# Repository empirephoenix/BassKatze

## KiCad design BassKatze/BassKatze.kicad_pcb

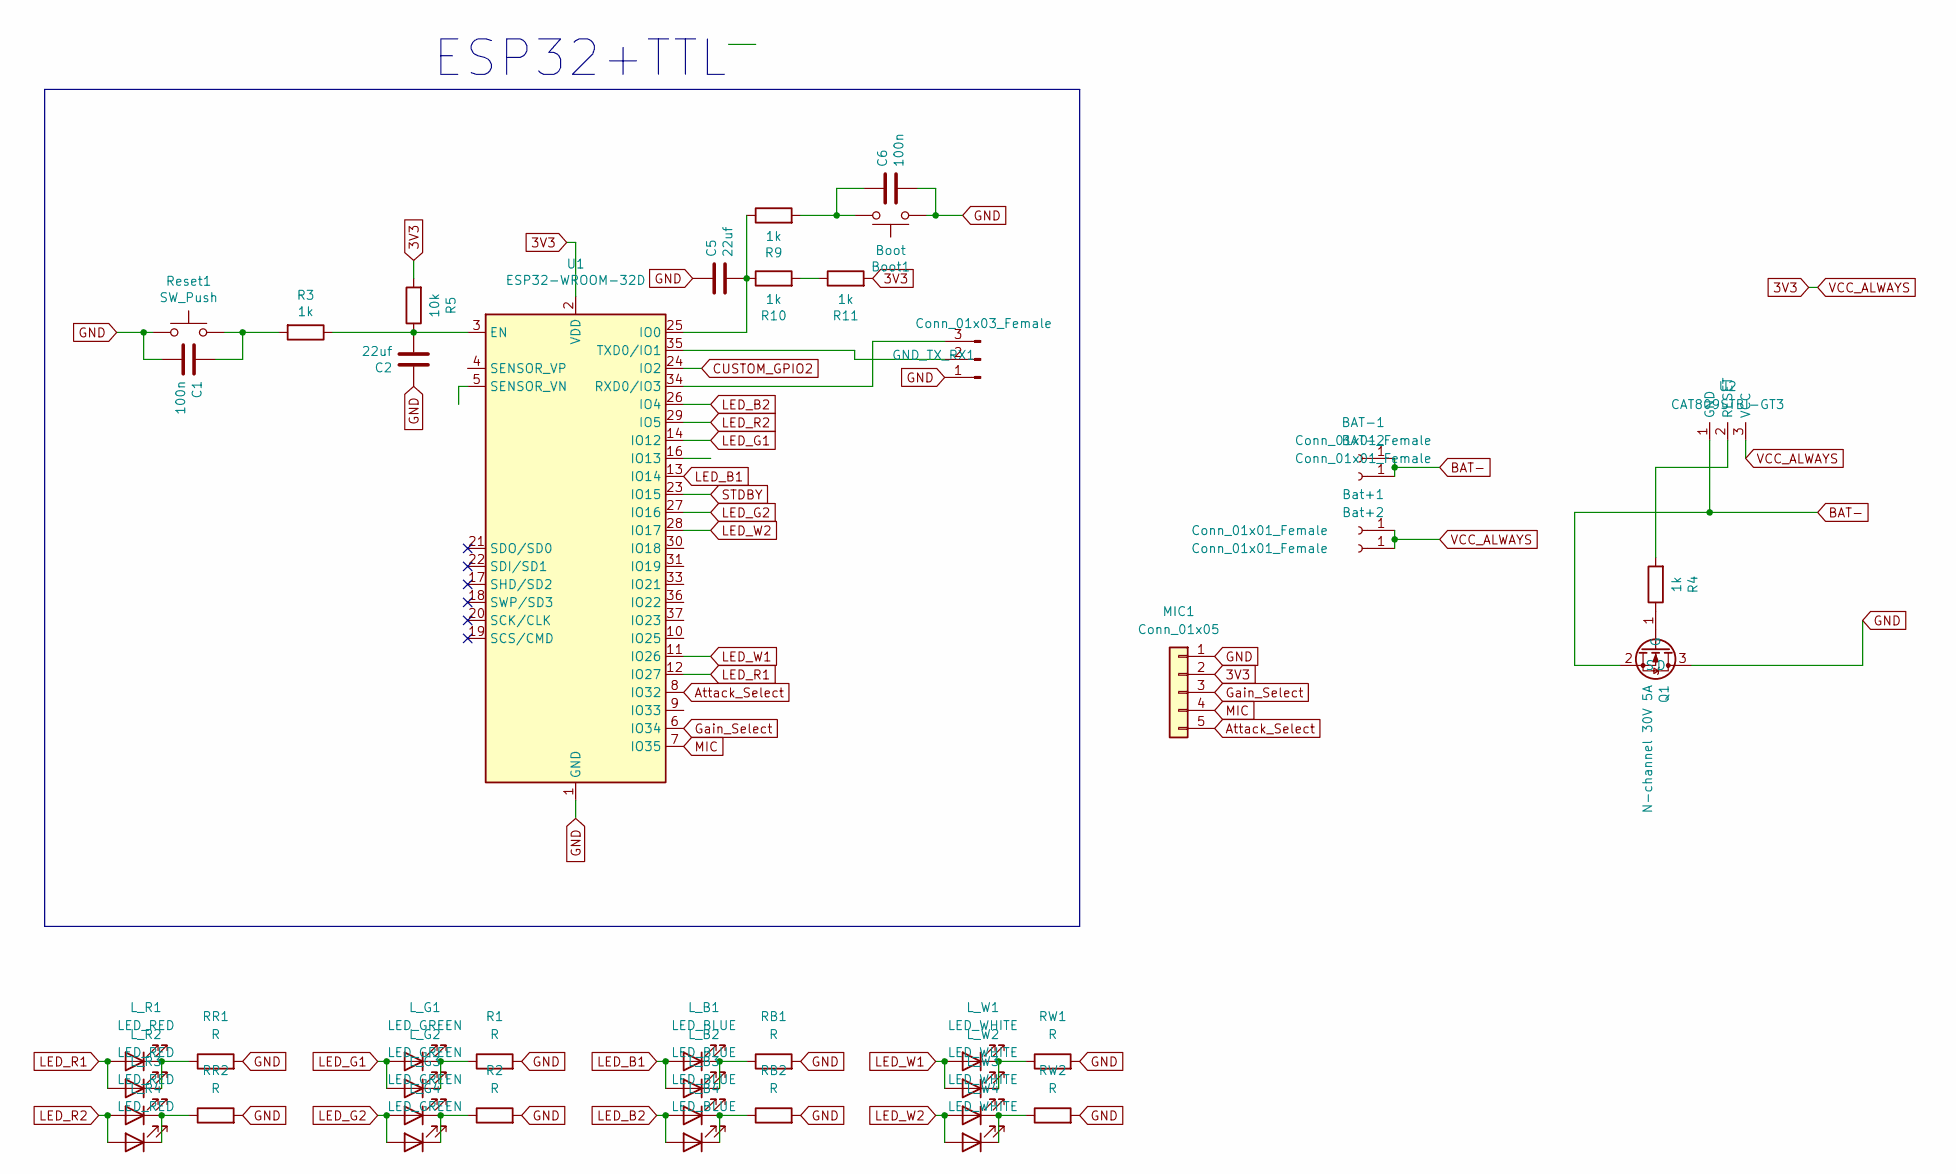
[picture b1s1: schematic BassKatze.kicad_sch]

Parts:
BAT-1, BAT-2: Conn_01x01_Female; SolderWirePad_1x01_SMD_5x10mm
Bat+1, Bat+2: Conn_01x01_Female; SolderWirePad_1x01_SMD_5x10mm
Boot1: Boot; SW_PUSH_6mm_H5mm; LCSC C72443
C1, C6: 100n; C_0805_2012Metric; LCSC C49678
C2, C5: 22uf; C_0805_2012Metric; LCSC C5674
GND_TX_RX1: Conn_01x03_Female; PinHeader_1x03_P2.54mm_Vertical; LCSC no
L_B1, L_B2, L_B3, L_B4: LED_BLUE; LED_0603_1608Metric
L_G1, L_G2, L_G3, L_G4: LED_GREEN; LED_0603_1608Metric
L_R1, L_R2, L_R3, L_R4: LED_RED; LED_0603_1608Metric
L_W1, L_W2, L_W3, L_W4: LED_WHITE; LED_0603_1608Metric
MIC1: Conn_01x05; PinHeader_1x05_P2.54mm_Vertical
Q1: N-channel 30V 5A; SOT-23; LCSC_PART_NUMBER C350314
R1, R2: R; R_0603_1608Metric
R3, R4, R9, R10, R11: 1k; R_0603_1608Metric; LCSC C21190
R5: 10k; R_0603_1608Metric; LCSC C25804
RB1, RB2: R; R_0603_1608Metric
RR1, RR2: R; R_0603_1608Metric
RW1, RW2: R; R_0603_1608Metric
Reset1: SW_Push; SW_SPST_CK_RS282G05A3; LCSC C72443
U1: ESP32-WROOM-32D; ESP32-WROOM-32; LCSC C529578
U2: CAT809STBI-GT3; SOT-23; LCSC C85255

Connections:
3V3: Bat+1.1, Bat+2.1, MIC1.2, R5.2, R11.2, U1.2 (VDD), U2.3 (VCC)
Attack_Select: MIC1.5, U1.8 (IO32)
BAT-: BAT-1.1, BAT-2.1, Q1.2 (S), U2.1 (GND)
CUSTOM_GPIO2: U1.24 (IO2)
GND: Boot1.1, C1.1, C2.1, C5.1, C6.1, GND_TX_RX1.1, MIC1.1, Q1.3 (D), R1.2, R2.2, RB1.2, RB2.2, RR1.2, RR2.2, RW1.2, RW2.2, Reset1.1, U1.1 (GND), U1.15 (GND), U1.38 (GND), U1.39 (GND)
Gain_Select: MIC1.3, U1.6 (IO34)
LED_B1: L_B1.2 (A), L_B2.2 (A), U1.13 (IO14)
LED_B2: L_B3.2 (A), L_B4.2 (A), U1.26 (IO4)
LED_G1: L_G1.2 (A), L_G2.2 (A), U1.14 (IO12)
LED_G2: L_G3.2 (A), L_G4.2 (A), U1.27 (IO16)
LED_R1: L_R1.2 (A), L_R2.2 (A), U1.12 (IO27)
LED_R2: L_R3.2 (A), L_R4.2 (A), U1.29 (IO5)
LED_W1: L_W1.2 (A), L_W2.2 (A), U1.11 (IO26)
LED_W2: L_W3.2 (A), L_W4.2 (A), U1.28 (IO17)
MIC: MIC1.4, U1.7 (IO35)
unnamed: Boot1.2, C6.2, R9.2
unnamed: C1.2, R3.2, Reset1.2
unnamed: C2.2, R3.1, R5.1, U1.3 (EN)
unnamed: C5.2, R9.1, R10.1, U1.25 (IO0)
unnamed: GND_TX_RX1.2, U1.35 (TXD0/IO1)
unnamed: GND_TX_RX1.3, U1.34 (RXD0/IO3)
unnamed: L_B1.1 (K), L_B2.1 (K), RB1.1
unnamed: L_B3.1 (K), L_B4.1 (K), RB2.1
unnamed: L_G1.1 (K), L_G2.1 (K), R1.1
unnamed: L_G3.1 (K), L_G4.1 (K), R2.1
unnamed: L_R1.1 (K), L_R2.1 (K), RR1.1
unnamed: L_R3.1 (K), L_R4.1 (K), RR2.1
unnamed: L_W1.1 (K), L_W2.1 (K), RW1.1
unnamed: L_W3.1 (K), L_W4.1 (K), RW2.1
unnamed: Q1.1 (G), R4.1
unnamed: R4.2, U2.2 (RESET)
unnamed: R10.2, R11.1
STDBY: U1.23 (IO15)

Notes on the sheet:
ESP32+TTL

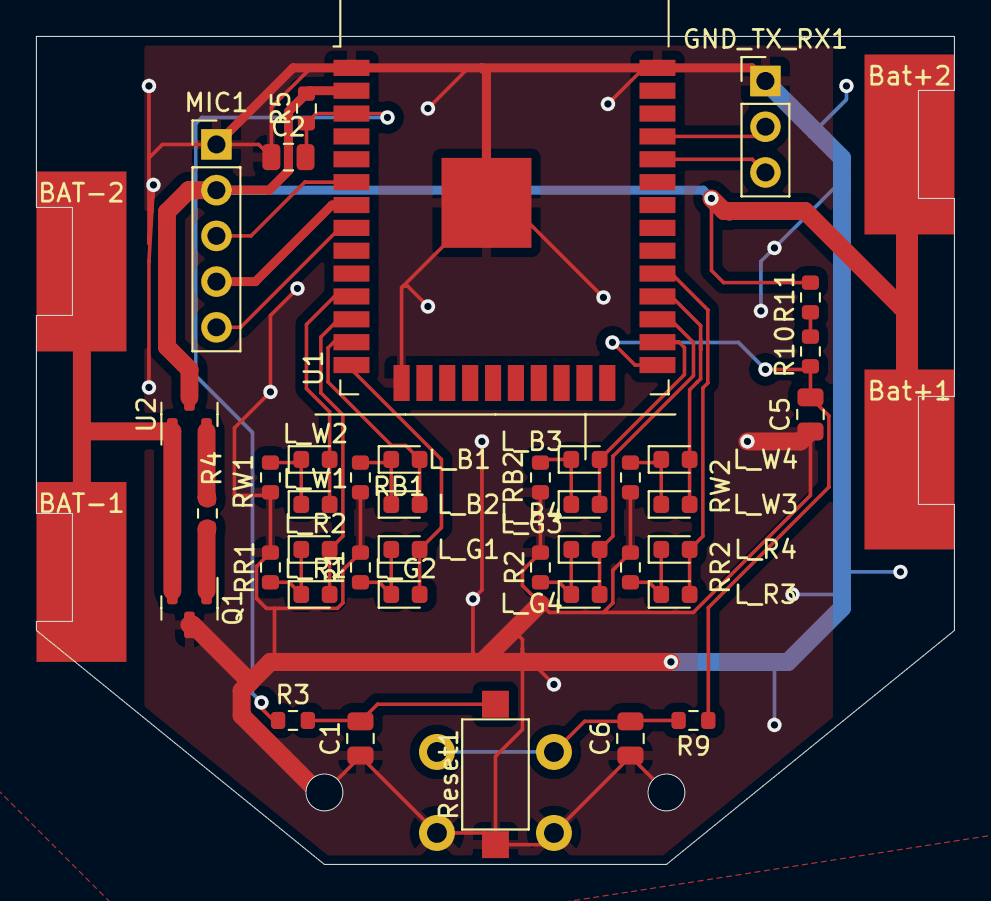
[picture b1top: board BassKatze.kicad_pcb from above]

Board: 2 copper layers, 51.0 x 46.0 mm, 45 parts (1 on the bottom side), 31 nets.

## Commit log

2019-10-18 init stuff
2019-10-19 basskatze wip 2
2019-10-20 pcb wip
2019-10-21 with mic amplifier
2019-10-22 Uploaded STL file for carrier/insert/mount
2019-10-22 added rx/tx header for serial debugging started dummy application
2019-10-22 added voltage measure prescaler
2019-11-06 Fixed wrong resistor (from 22k to 200k in oscilator microphone) Inital sketch
2019-11-07 added missing voltage divider for analog signal to atmega
2019-11-09 fixed mosfet power off circuit
2019-11-09 sync of annotations
2019-11-11 fixed charging circuit cuttoff not working, updated pcb to schematic
2019-11-18 force poweron, if isp is connected
2019-11-20 add pretective resistor to data pin of arduino
2019-11-22 Added version with NeoPixel Library
2019-11-22 NeoPixel version modified
2019-11-27 with median
2019-12-07 Added R16, added modes to sketch
2019-12-07 removed cache
2019-12-07 added brightness scall, and denoise
2019-12-07 fixed many shit
2019-12-13 Rev5 changes
2019-12-16 switch to msgeq7
2020-01-08 use TP5400 to remove issues with isp voltage
2020-01-15 update of the layout
2020-01-31 platformio change and bugfixes
2020-01-31 fixed description
2020-01-31 added missing librarys
2020-02-03 0.7 low voltage cutoff mosfet
2020-02-14 use voltage converters to prevent isp burnout
2020-02-17 tracing of 0.8 finished
2020-03-06 basskatze 0.9 -> removed redundant reset pullup
2020-07-30 basskatze 1.0 (fixed diode footprint, better manually solderable resistor arrays)
2022-08-03 update to esp32 proto
2022-09-16 esp32 version
2023-02-17 use hardware dma
2023-03-03 I2S FFT
2023-03-17 justierte Gewichtung der Frequenzbänder
